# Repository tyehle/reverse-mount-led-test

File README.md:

# Reverse Mount LED Test Board
Tiny board for testing reverse mount LED fit

# LICENSE

This work is licensed under a [Creative Commons Attribution-NonCommercial-ShareAlike 4.0 International License](http://creativecommons.org/licenses/by-nc-sa/4.0/).

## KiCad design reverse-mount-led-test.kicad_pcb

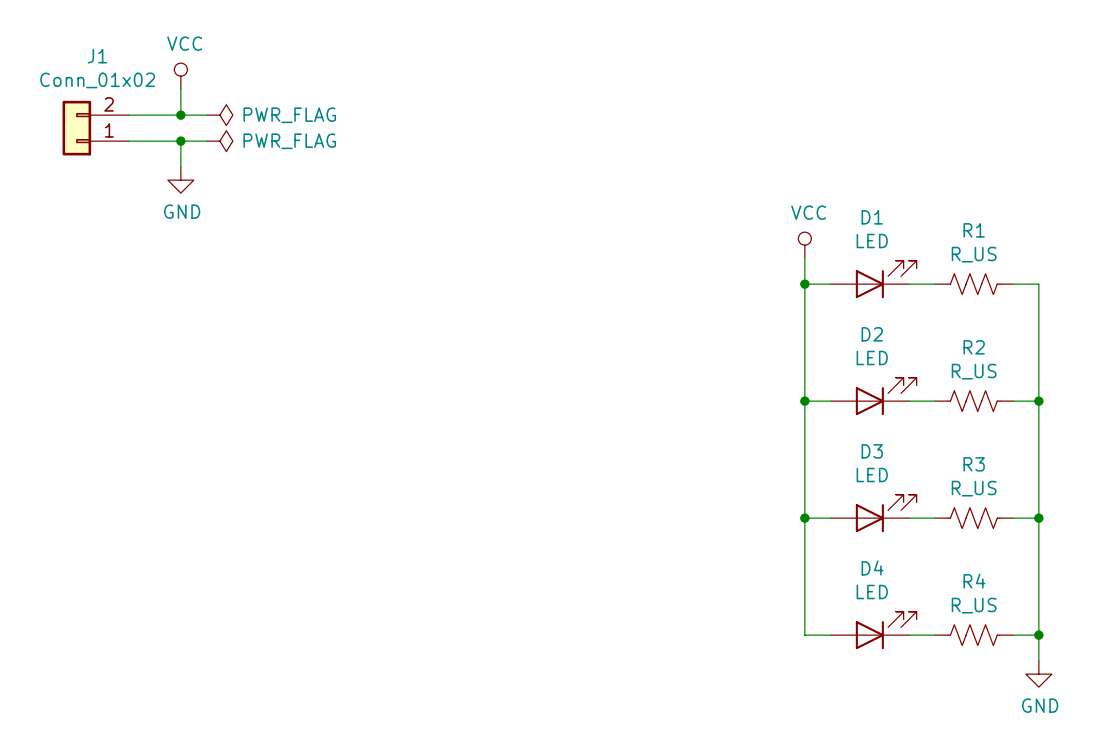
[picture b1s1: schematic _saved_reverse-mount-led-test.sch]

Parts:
D1, D2, D3, D4: LED; LED_1206_ReverseMountSquare1.5mm_HandSolder
J1: Conn_01x02; PinHeader_1x02_P2.54mm_Vertical
R1, R2, R3, R4: R_US; R_0805_2012Metric_Pad1.15x1.40mm_HandSolder

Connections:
GND: J1.1, R1.1, R2.1, R3.1, R4.1
unnamed: D1.1 (K), R1.2
unnamed: D2.1 (K), R2.2
unnamed: D3.1 (K), R3.2
unnamed: D4.1 (K), R4.2
VCC: D1.2 (A), D2.2 (A), D3.2 (A), D4.2 (A), J1.2

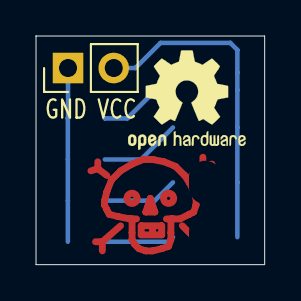
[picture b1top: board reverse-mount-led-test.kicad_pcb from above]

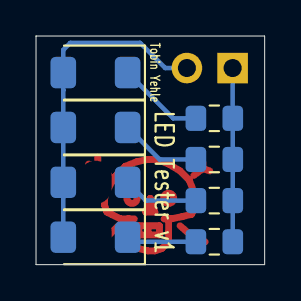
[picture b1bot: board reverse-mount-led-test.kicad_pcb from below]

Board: 2 copper layers, 12.7 x 12.7 mm, 9 parts (8 on the bottom side), 6 nets.

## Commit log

2019-07-10 basic schematic
2019-07-10 add README.md
2019-07-10 add footprints
2019-07-10 add netlist
2019-07-10 placement done
2019-07-10 setup design rules
2019-07-10 layout done
2019-07-10 decoration done
2019-07-10 add gerbers
2019-07-10 add render
2019-07-10 update render
2019-07-10 make render holes black
2019-07-10 add gerber zip
